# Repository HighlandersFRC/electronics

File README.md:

# Electronics Projects
Various electronics-related projects.

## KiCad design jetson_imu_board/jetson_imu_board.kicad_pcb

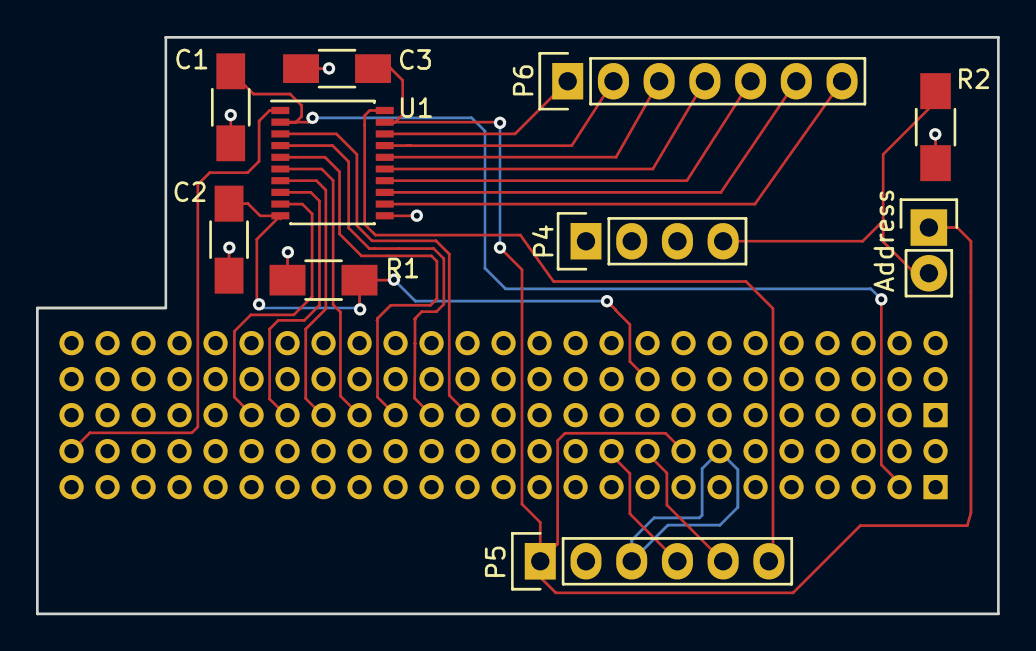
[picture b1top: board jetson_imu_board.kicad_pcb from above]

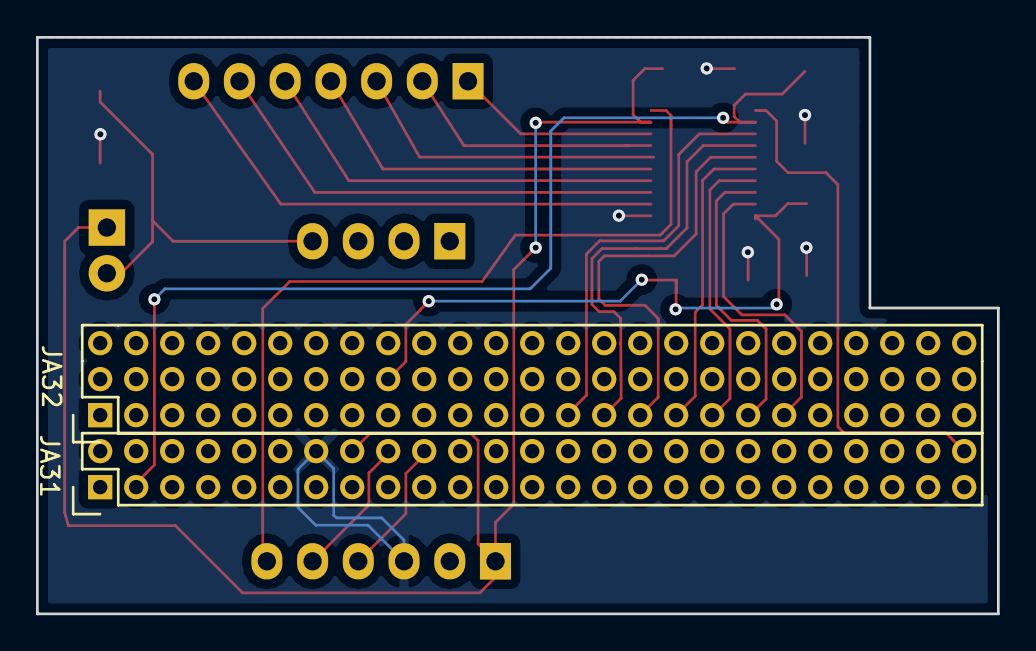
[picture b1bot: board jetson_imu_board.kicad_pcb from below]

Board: 2 copper layers, 53.4 x 32.0 mm, 12 parts (2 on the bottom side), 23 nets.

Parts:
Address: CONN_01X02; Pin_Header_Straight_1x02
C1, C3: 0.1u; C_1206_HandSoldering
C2: 1u; C_1206_HandSoldering
JA31: J3A1; Pin_Header_Straight_2x25_Pitch2.00mm
JA32: J3A2; Pin_Header_Straight_3x25_Pitch2.00mm
P4: CONN_01X04; Pin_Header_Straight_1x04
P5: CONN_01X06; Pin_Header_Straight_1x06
P6: CONN_01X07; Pin_Header_Straight_1x07
R1, R2: 10K; R_1206_HandSoldering
U1: TXB0108; SSOP-20_4.4x6.5mm_Pitch0.65mm

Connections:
/GPIO160_3V3: P6.1, U1.18
/GPIO161_3V3: P6.2, U1.17
/GPIO162_3V3: P6.3, U1.16
/GPIO163_3V3: P6.4, U1.15
/GPIO164_3V3: P6.5, U1.14
/GPIO165_3V3: P6.6, U1.13
/GPIO166_3V3: P6.7, U1.12
/IMU_ADR: Address.2, P4.4, R2.2
/IMU_RST: P5.6, U1.20
/JET_1V8: C1.1, JA31.3, U1.2
/JET_3V3: Address.1, C3.1, JA31.16, P5.1, U1.19
/JET_AMS_1V8: C2.1, JA32.26, R1.2, U1.10
/JET_GND: C1.2, C2.2, C3.2, JA31.14, P5.3, R1.1, R2.1, U1.11
/JET_GPIO57: JA31.50, U1.1
/JET_GPIO160: JA32.40, U1.3
/JET_GPIO161: JA32.43, U1.4
/JET_GPIO162: JA32.46, U1.5
/JET_GPIO163: JA32.49, U1.6
/JET_GPIO164: JA32.52, U1.7
/JET_GPIO165: JA32.55, U1.8
/JET_GPIO166: JA32.58, U1.9
/JET_SCL: JA31.18, P5.5
/JET_SDA: JA31.20, P5.4

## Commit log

2016-10-23 First commit of Jetson IMU daughterboard
2016-10-25 Switched to TXB0108 level shifter
2016-10-25 Added footprint associations, started board layout
2016-10-25 Fixed ERC rule violations
2016-10-29 Finished routing and layout
